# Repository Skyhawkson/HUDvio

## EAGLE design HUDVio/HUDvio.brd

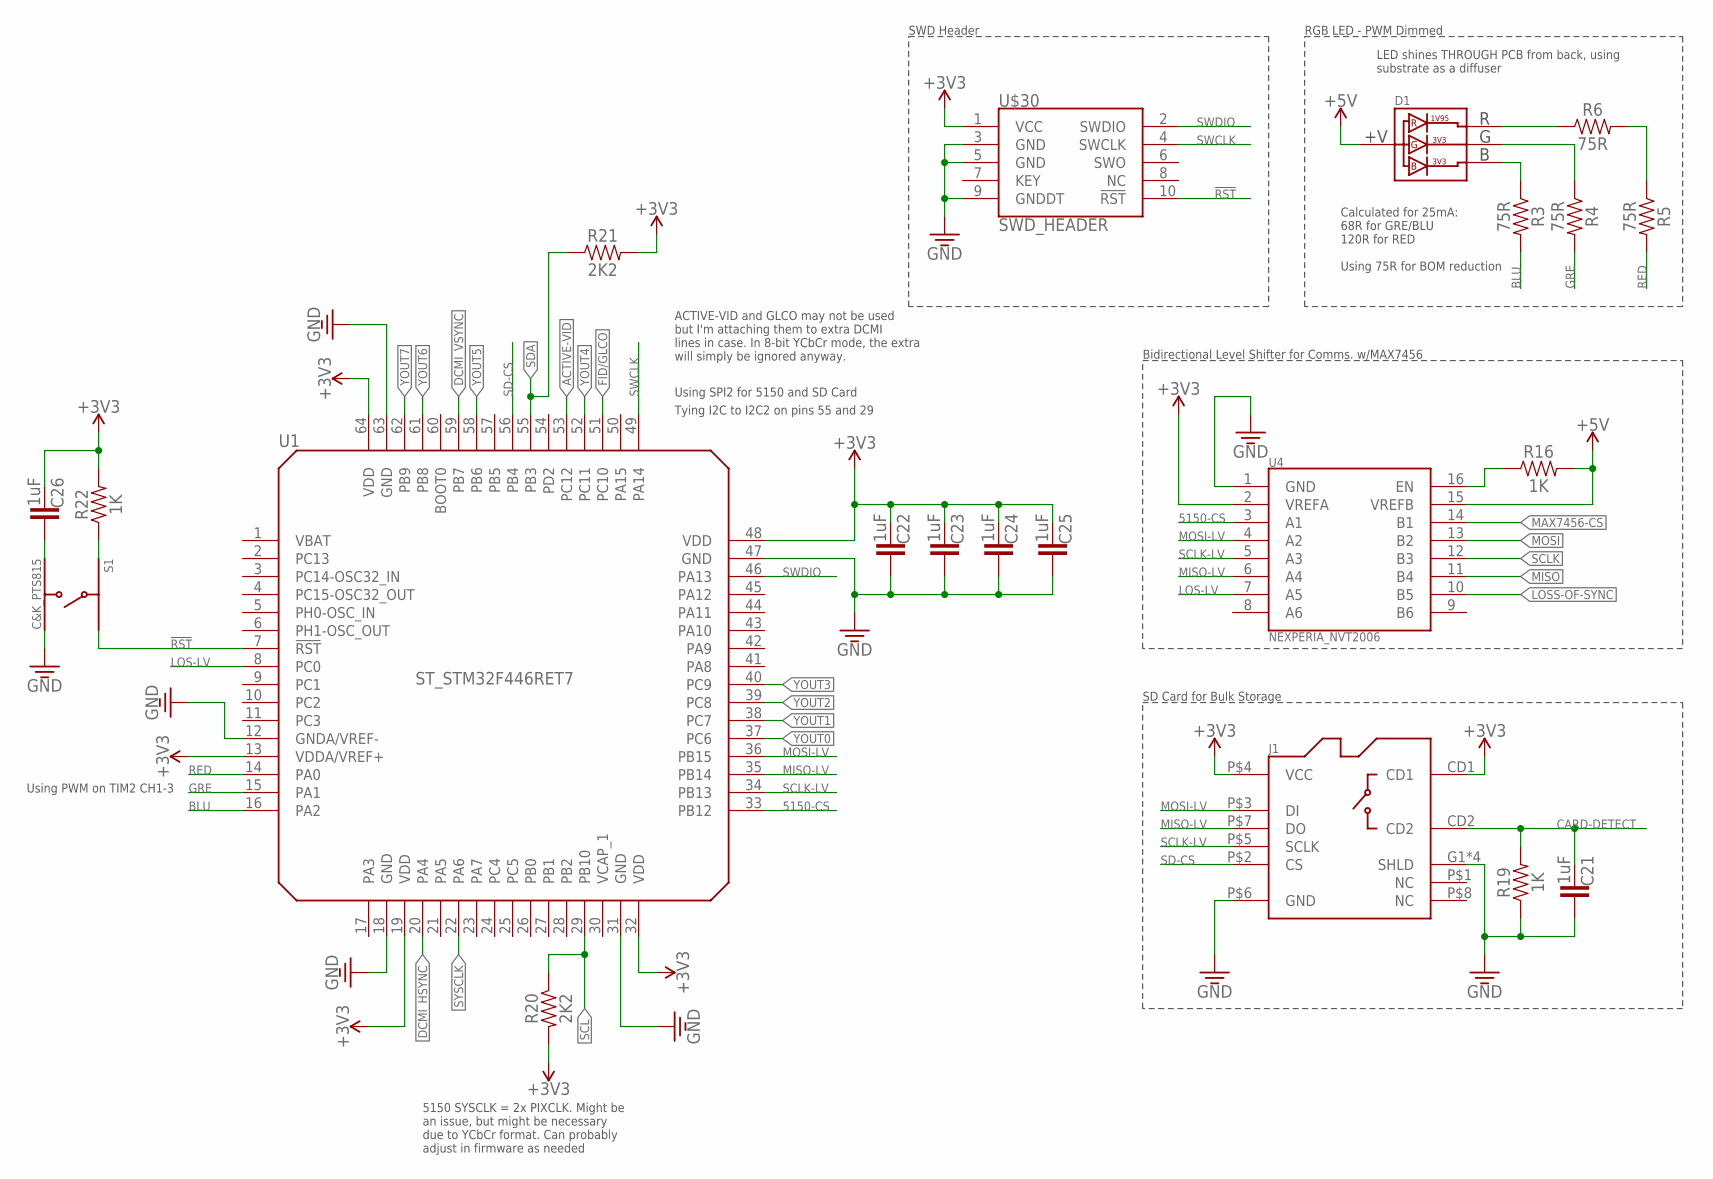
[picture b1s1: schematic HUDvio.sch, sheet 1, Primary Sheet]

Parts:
C21, C22, C23, C24, C25, C26: 1UF_0805; KEMET_0805
D1: SUNLED_XZMDKCBDDG45S-9; SUNLED_XZXXXXXX45S-9
J1: MOLEX_1040310811
R3, R4, R5, R6: 75R_0603; 0603
R16, R19, R22: 1K_0603; 0603
R20, R21: 2K2_0603; 0603
S1: C&K_PTS815
U1: ST_STM32F446RET7; ST_LQFP64
U4: NEXPERIA_NVT2006; NEXPERIA_SOT403-1_(TSSOP16)
U$30: SWD_HEADER; CNC_3220-10-0300-00

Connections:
5150-CS: U1.33 (PB12), U4.3 (A1)
!RST: S1.2, U1.7 (!RST!), U$30.10 (!RST!)
+3V3: C22.P$1 (1), C23.P$1 (1), C24.P$1 (1), C25.P$1 (1), C26.P$1 (1), J1.CD1, J1.P$4 (VCC), R20.2, R21.2, R22.2, U1.13 (VDDA/VREF+), U1.19 (VDD), U1.32 (VDD), U1.48 (VDD), U1.64 (VDD), U4.2 (VREFA), U$30.1 (VCC); also elsewhere on the board
+5V: D1.P$2 (VCC), R16.2, U4.15 (VREFB); also elsewhere on the board
ACTIVE-VID: U1.53 (PC12); also elsewhere on the board
BLU: R3.2, U1.16 (PA2)
CARD-DETECT: C21.P$1 (1), J1.CD2, R19.2
DCMI_HSYNC: U1.20 (PA4); also elsewhere on the board
DCMI_VSYNC: U1.59 (PB7); also elsewhere on the board
FID/GLCO: U1.51 (PC10); also elsewhere on the board
GND: C21.P$2 (2), C22.P$2 (2), C23.P$2 (2), C24.P$2 (2), C25.P$2 (2), J1.G1 (SHLD), J1.G2 (SHLD), J1.G3 (SHLD), J1.G4 (SHLD), J1.P$6 (GND), R19.1, S1.4, U1.12 (GNDA/VREF-), U1.18 (GND), U1.31 (GND), U1.47 (GND), U1.63 (GND), U4.1 (GND), U$30.3 (GND), U$30.5 (GND), U$30.9 (GNDDT); also elsewhere on the board
GRE: R4.2, U1.15 (PA1)
LOS-LV: U1.8 (PC0), U4.7 (A5)
LOSS-OF-SYNC: U4.10 (B5); also elsewhere on the board
MAX7456-CS: U4.14 (B1); also elsewhere on the board
MISO: U4.11 (B4); also elsewhere on the board
MISO-LV: J1.P$7 (DO), U1.35 (PB14), U4.6 (A4)
MOSI: U4.13 (B2); also elsewhere on the board
MOSI-LV: J1.P$3 (DI), U1.36 (PB15), U4.4 (A2)
unnamed: D1.P$1 (R), R6.1
unnamed: R5.1, R6.2
unnamed: D1.P$4 (G), R4.1
unnamed: D1.P$3 (B), R3.1
unnamed: R16.1, U4.16 (EN)
unnamed: R22.1, S1.1
unnamed: C26.P$2 (2), S1.3
RED: R5.2, U1.14 (PA0)
SCL: R20.1, U1.29 (PB10); also elsewhere on the board
SCLK: U4.12 (B3); also elsewhere on the board
SCLK-LV: J1.P$5 (SCLK), U1.34 (PB13), U4.5 (A3)
SD-CS: J1.P$2 (CS), U1.56 (PB4)
SDA: R21.1, U1.55 (PB3); also elsewhere on the board
SWCLK: U1.49 (PA14), U$30.4 (SWCLK)
SWDIO: U1.46 (PA13), U$30.2 (SWDIO)
SYSCLK: U1.22 (PA6); also elsewhere on the board
VBAT: U1.1 (VBAT)
VCAP_1: U1.30 (VCAP_1)
YOUT0: U1.37 (PC6); also elsewhere on the board
YOUT1: U1.38 (PC7); also elsewhere on the board
YOUT2: U1.39 (PC8); also elsewhere on the board
YOUT3: U1.40 (PC9); also elsewhere on the board
YOUT4: U1.52 (PC11); also elsewhere on the board
YOUT5: U1.58 (PB6); also elsewhere on the board
YOUT6: U1.61 (PB8); also elsewhere on the board
YOUT7: U1.62 (PB9); also elsewhere on the board

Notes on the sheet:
Calculated for 25mA: 68R for GRE/BLU 120R for RED Using 75R for BOM reduction
LED shines THROUGH PCB from back, using substrate as a diffuser
RGB LED - PWM Dimmed
Bidirectional Level Shifter for Comms. w/MAX7456
5150 SYSCLK = 2x PIXCLK. Might be an issue, but might be necessary due to YCbCr format. Can probably adjust in firmware as needed
SD Card for Bulk Storage
ACTIVE-VID and GLCO may not be used but I'm attaching them to extra DCMI lines in case. In 8-bit YCbCr mode, the extra will simply be ignored anyway.
Using SPI2 for 5150 and SD Card
Using PWM on TIM2 CH1-3
Tying I2C to I2C2 on pins 55 and 29
SWD Header

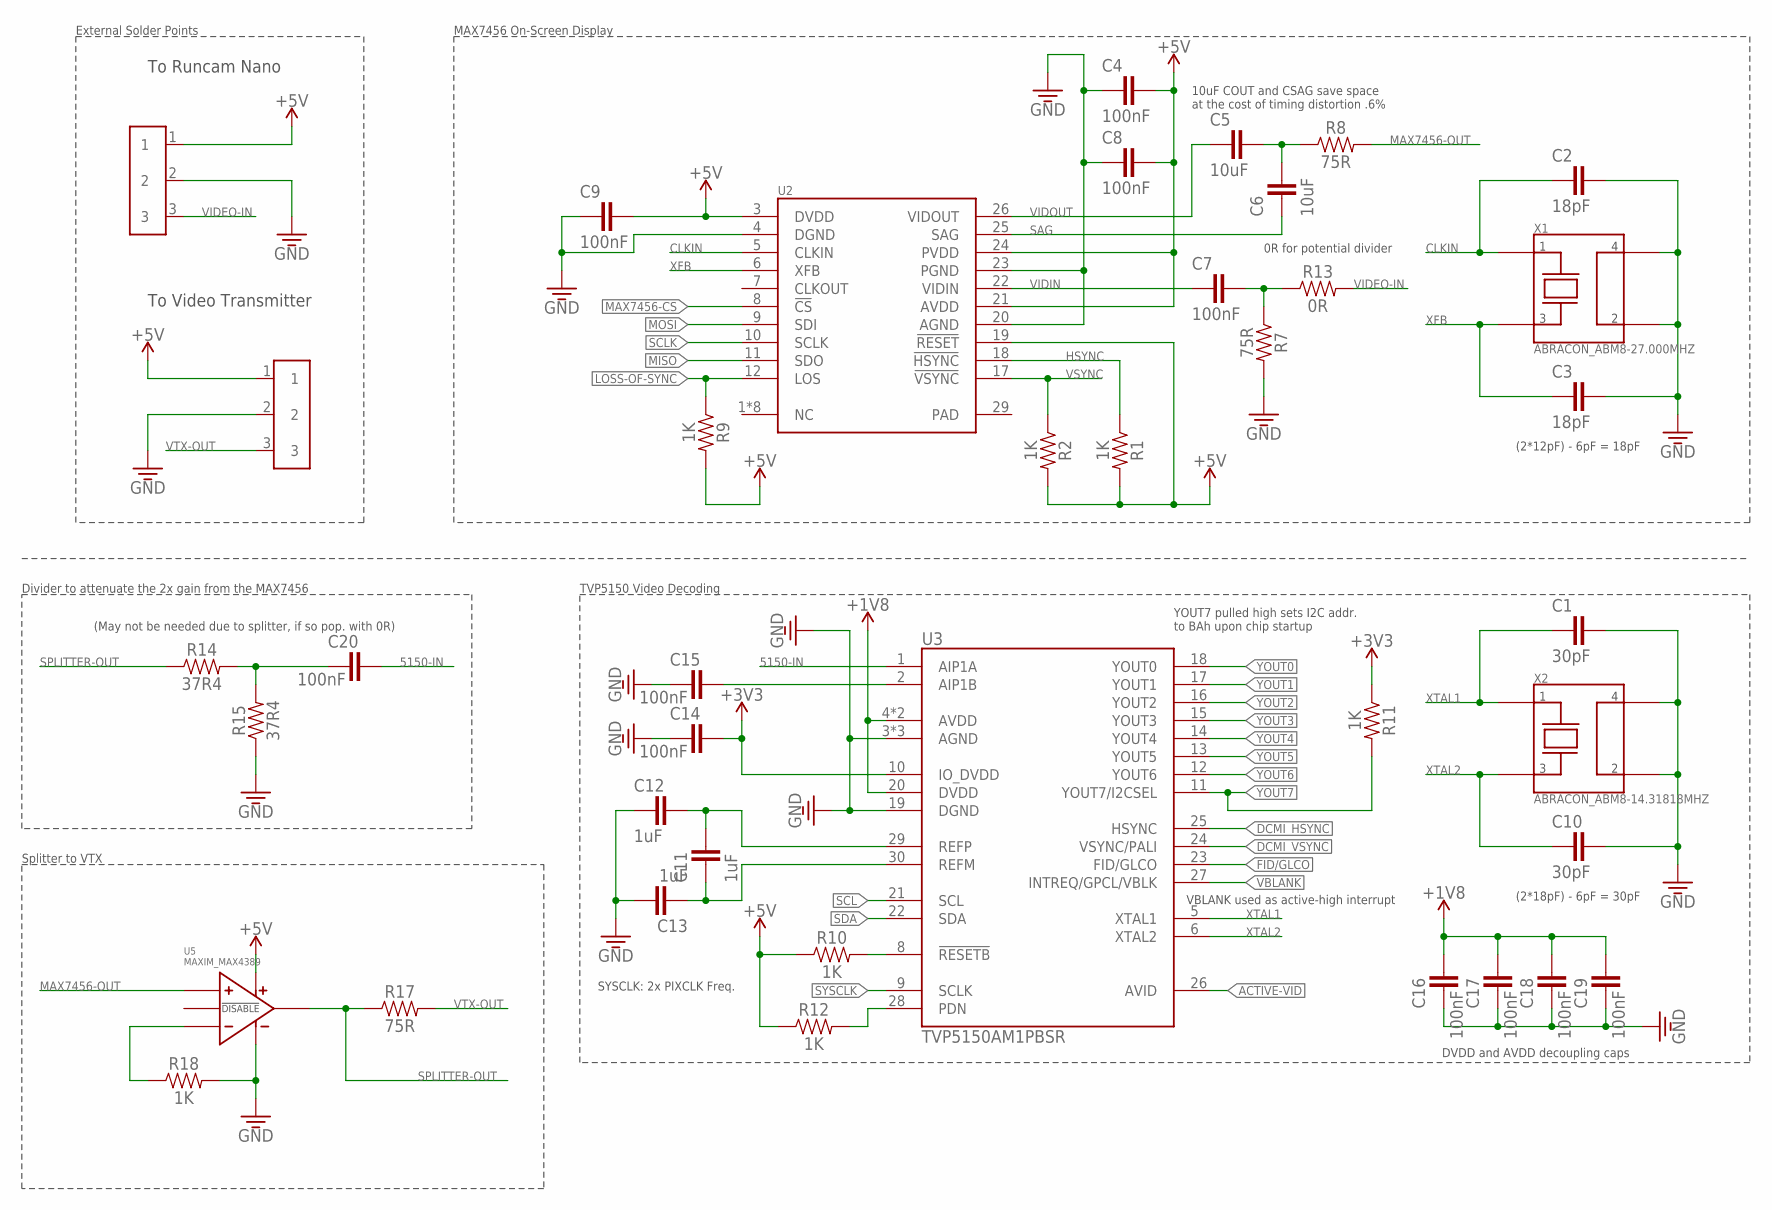
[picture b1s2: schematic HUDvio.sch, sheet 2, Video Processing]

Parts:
C1, C10: 30PF_0805; KEMET_0805
C2, C3: 18PF_0805; KEMET_0805
C4, C7, C8, C9, C14, C15, C16, C17, C18, C19, C20: 100NF_0805; KEMET_0805
C5, C6: 10UF_0805; KEMET_0805
C11, C12, C13: 1UF_0805; KEMET_0805
R1, R2, R9, R10, R11, R12, R18: 1K_0603; 0603
R7, R8, R17: 75R_0603; 0603
R13: 0R_0603; 0603
R14, R15: 37R4_0603; 0603
U2: MAXIM_MAX7456; MAXIM_MAX7456EUI+T
U3: TVP5150AM1PBSR; TI_PBS_(S-PQFP-G32)
U5: MAXIM_MAX4389; MAXIM_21-0058_(SOT23-6)
U$1, U$3: SOLDER_PAD_1X3; SOLDER_PAD_1X3_3X2MM
X1: ABRACON_ABM8-27.000MHZ; ABRACON_ABM8
X2: ABRACON_ABM8-14.31818MHZ; ABRACON_ABM8

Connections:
5150-IN: C20.P$2 (2), U3.1 (AIP1A)
$NET11: C7.P$2 (2), R7.1, R13.1
+1V8: C16.P$2 (2), C17.P$2 (2), C18.P$2 (2), C19.P$2 (2), U3.4 (AVDD), U3.20 (DVDD), U3.32 (AVDD); also elsewhere on the board
+3V3: C14.P$2 (2), R11.1, U3.10 (IO_DVDD); also elsewhere on the board
+5V: C4.P$2 (2), C8.P$2 (2), C9.P$2 (2), R9.2, R10.1, R12.1, U2.3 (DVDD), U2.21 (AVDD), U2.24 (PVDD), U5.6 (VCC), U$1.1, U$3.1; also elsewhere on the board
ACTIVE-VID: U3.26 (AVID); also elsewhere on the board
CLKIN: C2.P$1 (1), U2.5 (CLKIN), X1.1
DCMI_HSYNC: U3.25 (HSYNC); also elsewhere on the board
DCMI_VSYNC: U3.24 (VSYNC/PALI); also elsewhere on the board
FID/GLCO: U3.23 (FID/GLCO); also elsewhere on the board
GND: C1.P$2 (2), C2.P$2 (2), C3.P$2 (2), C4.P$1 (1), C8.P$1 (1), C9.P$1 (1), C10.P$2 (2), C12.P$1 (1), C13.P$2 (2), C14.P$1 (1), C15.P$1 (1), C16.P$1 (1), C17.P$1 (1), C18.P$1 (1), C19.P$1 (1), R7.2, R15.1, R18.2, U2.4 (DGND), U2.20 (AGND), U2.23 (PGND), U3.3 (AGND), U3.7 (AGND), U3.19 (DGND), U3.31 (AGND), U5.2 (VEE), U$1.2, U$3.2, X1.2, X1.4, X2.2, X2.4; also elsewhere on the board
HSYNC: R1.1, U2.18 (!HSYNC!)
LOSS-OF-SYNC: R9.1, U2.12 (LOS); also elsewhere on the board
MAX7456-CS: U2.8 (!CS!); also elsewhere on the board
MAX7456-OUT: R8.2
MISO: U2.11 (SDO); also elsewhere on the board
MOSI: U2.9 (SDI); also elsewhere on the board
unnamed: R1.2, R2.2, U2.19 (!RESET!)
unnamed: R10.2, U3.8 (!RESETB!)
unnamed: R12.2, U3.28 (PDN)
unnamed: C11.P$1 (1), C13.P$1 (1), U3.30 (REFM)
unnamed: C11.P$2 (2), C12.P$2 (2), U3.29 (REFP)
unnamed: C5.P$2 (2), C6.P$2 (2), R8.1
unnamed: C20.P$1 (1), R14.2, R15.2
unnamed: C15.P$2 (2), U3.2 (AIP1B)
unnamed: R18.1, U5.4 (IN-)
PAD: U2.29 (PAD)
SAG: C6.P$1 (1), U2.25 (SAG)
SCL: U3.21 (SCL); also elsewhere on the board
SCLK: U2.10 (SCLK); also elsewhere on the board
SDA: U3.22 (SDA); also elsewhere on the board
SPLITTER-OUT: R14.1, R17.1, U5.1 (OUT)
SYSCLK: U3.9 (SCLK); also elsewhere on the board
VBLANK: U3.27 (INTREQ/GPCL/VBLK)
VIDEO-IN: R13.2, U$1.3
VIDIN: C7.P$1 (1), U2.22 (VIDIN)
VIDOUT: C5.P$1 (1), U2.26 (VIDOUT)
VSYNC: R2.1, U2.17 (!VSYNC!)
VTX-OUT: R17.2, U$3.3
XFB: C3.P$1 (1), U2.6 (XFB), X1.3
XTAL1: C1.P$1 (1), U3.5 (XTAL1), X2.1
XTAL2: C10.P$1 (1), U3.6 (XTAL2), X2.3
YOUT0: U3.18 (YOUT0); also elsewhere on the board
YOUT1: U3.17 (YOUT1); also elsewhere on the board
YOUT2: U3.16 (YOUT2); also elsewhere on the board
YOUT3: U3.15 (YOUT3); also elsewhere on the board
YOUT4: U3.14 (YOUT4); also elsewhere on the board
YOUT5: U3.13 (YOUT5); also elsewhere on the board
YOUT6: U3.12 (YOUT6); also elsewhere on the board
YOUT7: R11.2, U3.11 (YOUT7/I2CSEL); also elsewhere on the board

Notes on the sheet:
To Runcam Nano
To Video Transmitter
(2*12pF) - 6pF = 18pF
10uF COUT and CSAG save space at the cost of timing distortion .6%
(2*18pF) - 6pF = 30pF
SYSCLK: 2x PIXCLK Freq.
YOUT7 pulled high sets I2C addr. to BAh upon chip startup
VBLANK used as active-high interrupt
0R for potential divider
Divider to attenuate the 2x gain from the MAX7456
DVDD and AVDD decoupling caps
TVP5150 Video Decoding
External Solder Points
MAX7456 On-Screen Display
Splitter to VTX
(May not be needed due to splitter, if so pop. with 0R)

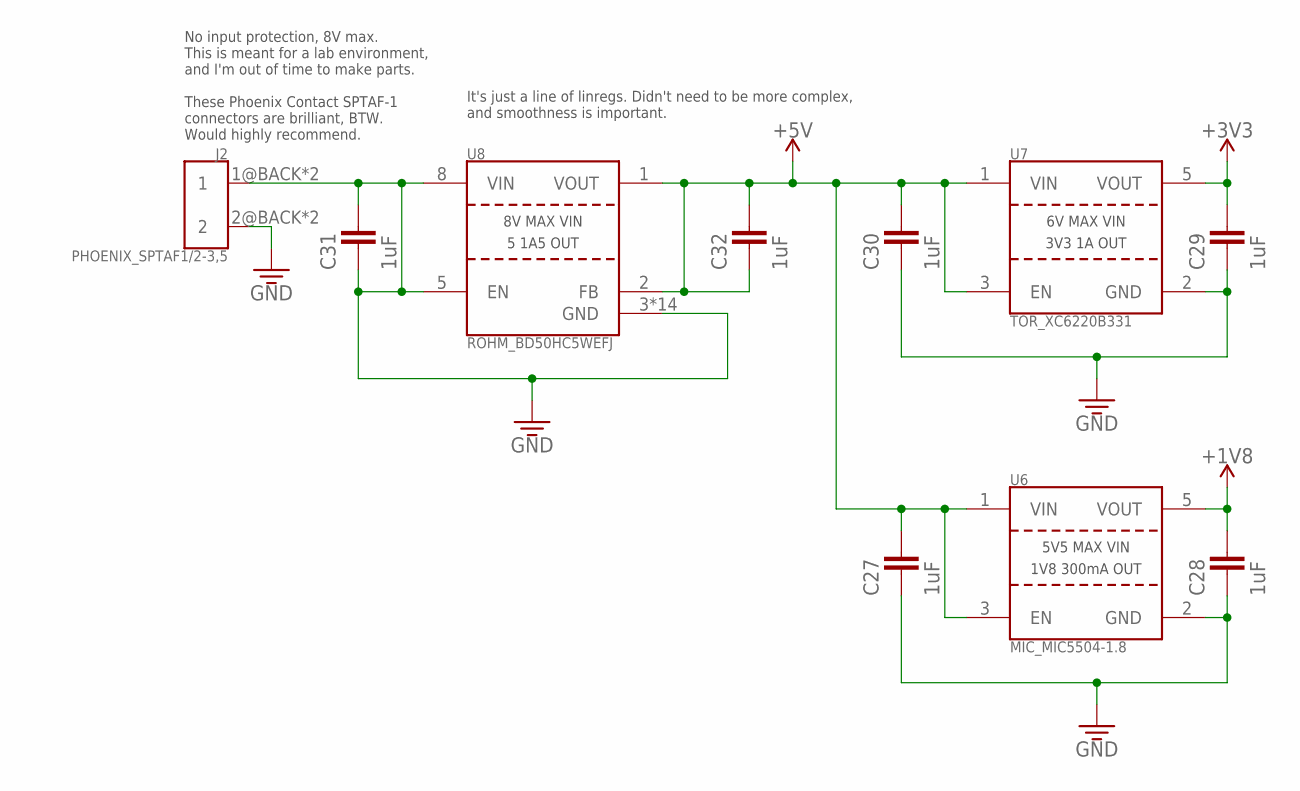
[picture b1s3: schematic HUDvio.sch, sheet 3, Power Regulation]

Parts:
C27, C28, C29, C30, C31, C32: 1UF_0805; KEMET_0805
J2: PHOENIX_SPTAF1/2-3,5; PHOENIX_SPTAF1/X-3,5
U6: MIC_MIC5504-1.8; MIC_SOT23-5LD-PL-1
U7: TOR_XC6220B331; TOR_SOT-25
U8: ROHM_BD50HC5WEFJ; ROHM_HTSOP-J8

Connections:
+1V8: C28.P$2 (2), U6.5 (VOUT); also elsewhere on the board
+3V3: C29.P$2 (2), U7.5 (VOUT); also elsewhere on the board
+5V: C27.P$2 (2), C30.P$2 (2), C32.P$1 (1), C32.P$2 (2), U6.1 (VIN), U6.3 (EN), U7.1 (VIN), U7.3 (EN), U8.1 (VOUT), U8.2 (FB); also elsewhere on the board
GND: C27.P$1 (1), C28.P$1 (1), C31.P$1 (1), C31.P$2 (2), J2.1@BACK (1), J2.1@FRONT (1), J2.2@BACK (2), J2.2@FRONT (2), U6.2 (GND), U8.3 (GND), U8.5 (EN), U8.8 (VIN), U8.FIN (GND), U8.FIN10 (GND), U8.FIN11 (GND), U8.FIN14 (GND), U8.FIN20 (GND), U8.FIN21 (GND), U8.FIN22 (GND), U8.FIN23 (GND), U8.FIN24 (GND), U8.FIN30 (GND), U8.FIN31 (GND), U8.FIN33 (GND), U8.FIN34 (GND); also elsewhere on the board
unnamed: C29.P$1 (1), C30.P$1 (1), U7.2 (GND)

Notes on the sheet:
It's just a line of linregs. Didn't need to be more complex, and smoothness is important.
No input protection, 8V max. This is meant for a lab environment, and I'm out of time to make parts.
These Phoenix Contact SPTAF-1 connectors are brilliant, BTW. Would highly recommend.

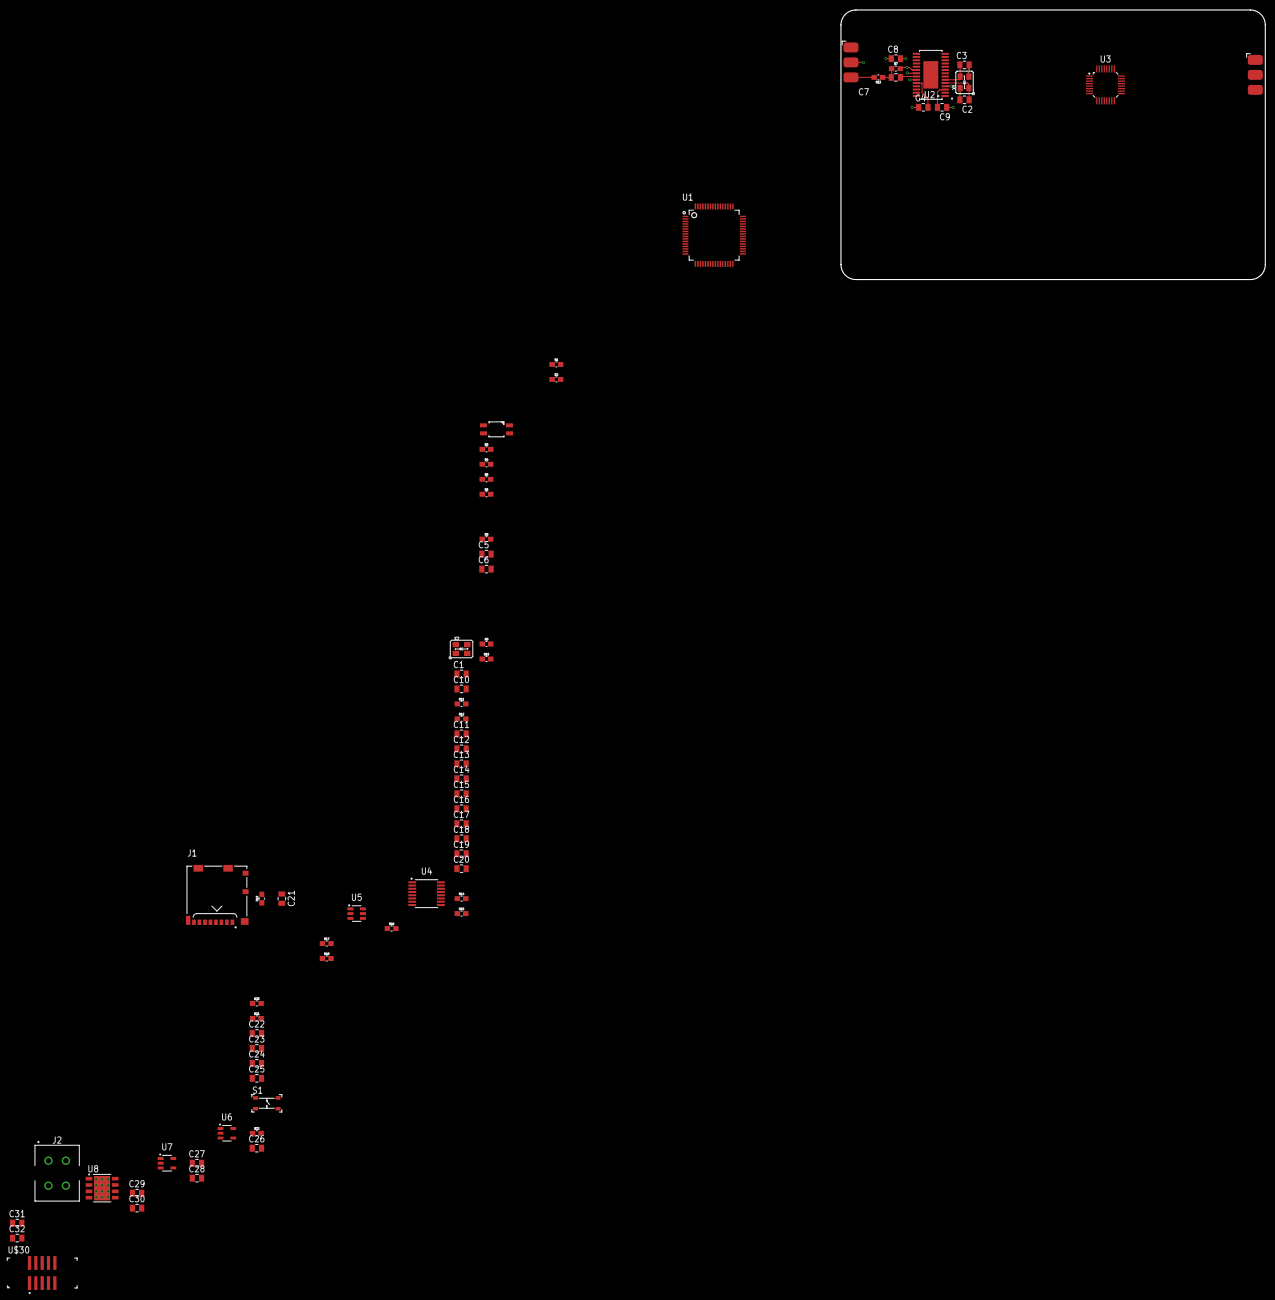
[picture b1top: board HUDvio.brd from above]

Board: 4 copper layers, 85.0 x 54.0 mm, 71 parts (0 on the bottom side), 68 nets.

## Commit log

2021-01-14 Added branch and started schematic
2021-01-14 Added board and rounded corners
2021-01-14 Completed Prelim. Sys Architecture
2021-01-14 Started video sheet
2021-01-14 Pre dinner commit
2021-01-14 Added layer stackup
2021-01-15 Lots of shit. Added splitter
2021-01-15 Ran DCMI pins
2021-01-15 Added uSD card
2021-01-15 Assigned more pins
2021-01-15 Added 3rd sheet
2021-01-15 Schematic done, moving to Board
2021-01-15 Schematic Complete
2021-01-15 Started Layout
